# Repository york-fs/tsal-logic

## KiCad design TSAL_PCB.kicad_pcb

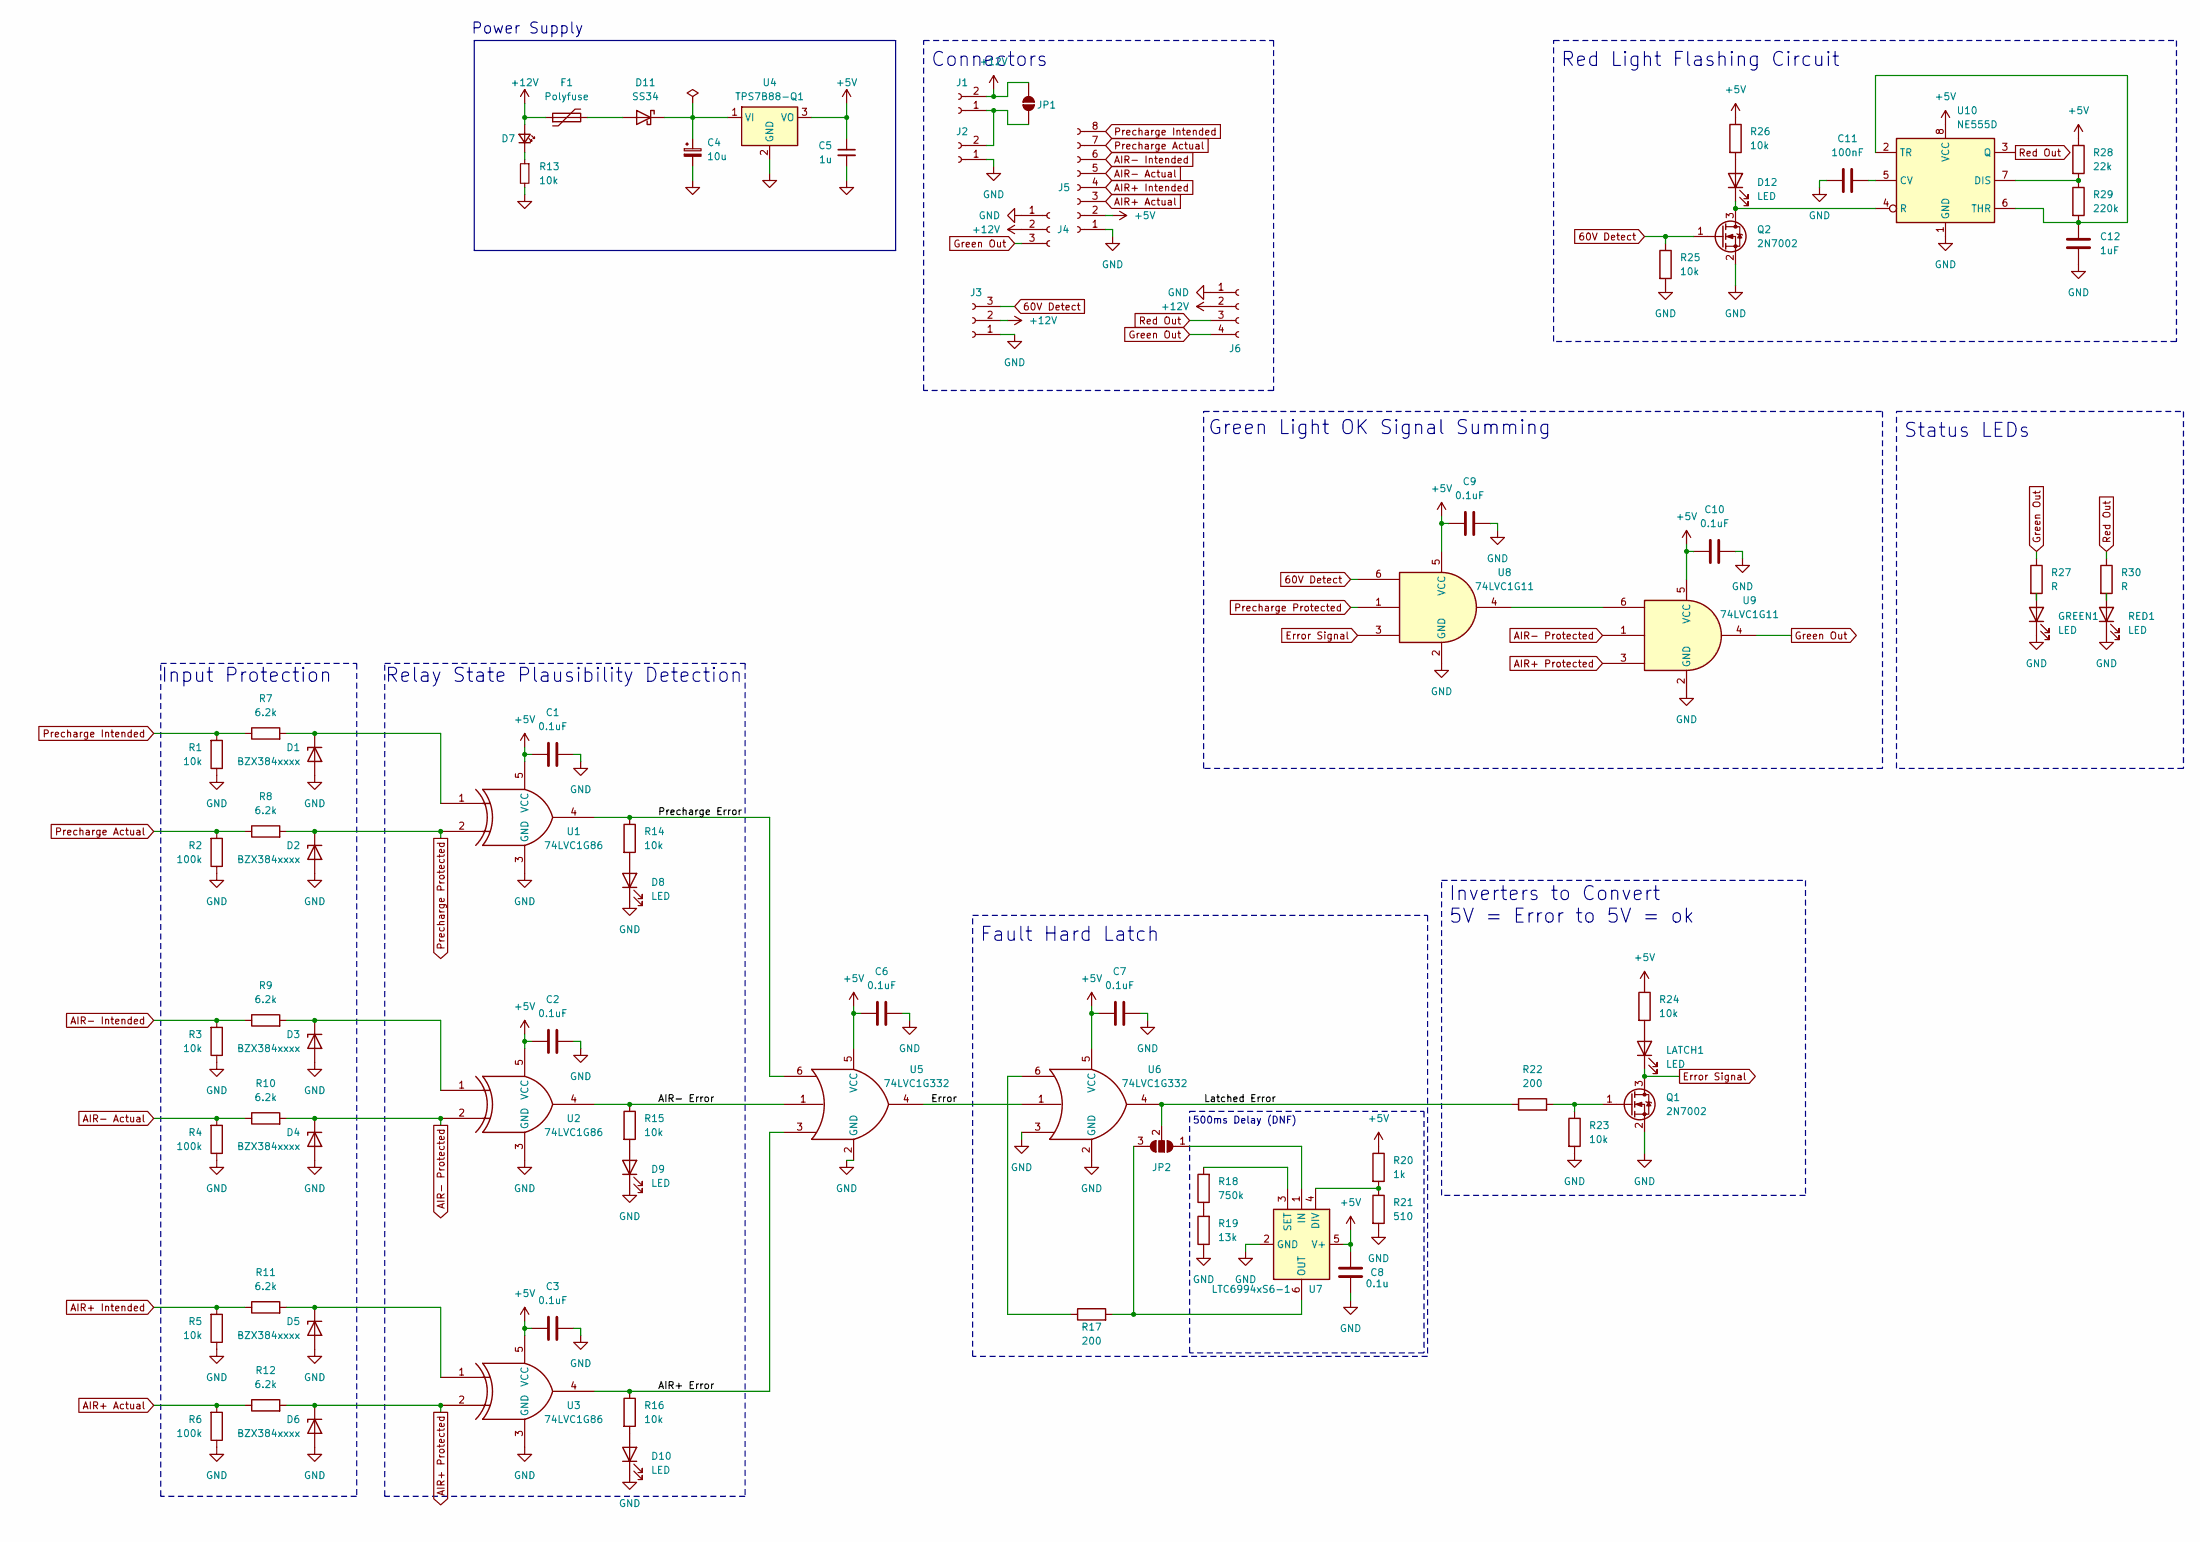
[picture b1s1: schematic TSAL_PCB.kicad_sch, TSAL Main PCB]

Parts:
C1, C2, C3, C6, C7, C9, C10: 0.1uF; C_0603_1608Metric
C4: 10u; CP_Elec_6.3x5.4
C5: 1u; C_0603_1608Metric
C8: 0.1u; C_0603_1608Metric
C11: 100nF; C_0603_1608Metric
C12: 1uF; C_0603_1608Metric
D1, D2, D3, D4, D5, D6: BZX384xxxx; D_SOD-323
D7: LED_Small; LED_0603_1608Metric
D8, D9, D10, D12: LED; LED_0603_1608Metric
D11: SS34; D_SMA
F1: Polyfuse; R_0805_2012Metric
GREEN1: LED; LED_0603_1608Metric
J1, J2: Conn_01x02_Socket; MolexMicrofitPlus1x2
J3, J4: Conn_01x03_Socket; MolexMicrofitPlus1x3
J5: Conn_01x08_Socket; MolexMicrofitPlus1x8
J6: Conn_01x04_Socket; MolexMicrofitPlus1x4
JP1: SolderJumper_2_Open; SolderJumper-2_P1.3mm_Open_RoundedPad1.0x1.5mm
JP2: SolderJumper_3_Open; SolderJumper-3_P1.3mm_Open_RoundedPad1.0x1.5mm_NumberLabels
LATCH1: LED; LED_0603_1608Metric
Q1, Q2: 2N7002; SOT-23
R1, R3, R5, R13, R14, R15, R16, R23, R24, R25, R26: 10k; R_0603_1608Metric
R2, R4, R6: 100k; R_0603_1608Metric
R7, R8, R9, R10, R11, R12: 6.2k; R_0603_1608Metric
R17, R22: 200; R_0603_1608Metric
R18: 750k; R_0603_1608Metric
R19: 13k; R_0603_1608Metric
R20: 1k; R_0603_1608Metric
R21: 510; R_0603_1608Metric
R27, R30: R; R_0603_1608Metric
R28: 22k; R_0603_1608Metric
R29: 220k; R_0603_1608Metric
RED1: LED; LED_0603_1608Metric
U1, U2, U3: 74LVC1G86; SOT-23-5
U4: TPS7B88-Q1; TO-252-2
U5, U6: 74LVC1G332; SOT-23-6
U7: LTC6994xS6-1; TSOT-23-6
U8, U9: 74LVC1G11; SOT-23-6
U10: NE555D; SOIC-8_3.9x4.9mm_P1.27mm

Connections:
60V Detect: J3.3, Q2.1 (G), R25.1, U8.6
+5V: C1.1, C2.1, C3.1, C5.1, C6.1, C7.1, C8.2, C9.1, C10.1, J5.2, R20.1, R24.1, R26.1, R28.1, U1.5 (VCC), U2.5 (VCC), U3.5 (VCC), U4.3 (VO), U5.5 (VCC), U6.5 (VCC), U7.5 (V+), U8.5 (VCC), U9.5 (VCC), U10.8 (VCC)
+12V: D7.2 (A), F1.1, J1.2, J3.2, J4.2, J6.2, JP1.2 (B)
/AIR+ Error: R16.1, U3.4, U5.3
/AIR- Error: R15.1, U2.4, U5.1
/Error: U5.4, U6.1
/Latched Error: JP2.2 (C), R22.1, U6.4
/Precharge Error: R14.1, U1.4, U5.6
AIR+ Actual: J5.3, R6.2, R12.1
AIR+ Intended: J5.4, R5.2, R11.1
AIR+ Protected: D6.1 (K), R12.2, U3.2, U9.3
AIR- Actual: J5.5, R4.2, R10.1
AIR- Intended: J5.6, R3.2, R9.1
AIR- Protected: D4.1 (K), R10.2, U2.2, U9.1
Error Signal: LATCH1.1 (K), Q1.3 (D), U8.3
GND: C1.2, C2.2, C3.2, C4.2, C5.2, C6.2, C7.2, C8.1, C9.2, C10.2, C11.2, C12.1, D1.2 (A), D2.2 (A), D3.2 (A), D4.2 (A), D5.2 (A), D6.2 (A), D8.1 (K), D9.1 (K), D10.1 (K), GREEN1.1 (K), J2.1, J3.1, J4.1, J5.1, J6.1, Q1.2 (S), Q2.2 (S), R1.1, R2.1, R3.1, R4.1, R5.1, R6.1, R13.2, R19.1, R21.2, R23.2, R25.2, RED1.1 (K), U1.3 (GND), U2.3 (GND), U3.3 (GND), U4.2 (GND), U5.2 (GND), U6.2 (GND), U6.3, U7.2 (GND), U8.2 (GND), U9.2 (GND), U10.1 (GND)
Green Out: J4.3, J6.4, R27.1, U9.4
unnamed: D1.1 (K), R7.2, U1.1
unnamed: D3.1 (K), R9.2, U2.1
unnamed: D5.1 (K), R11.2, U3.1
unnamed: D7.1 (K), R13.1
unnamed: D8.2 (A), R14.2
unnamed: D9.2 (A), R15.2
unnamed: D10.2 (A), R16.2
unnamed: D11.2 (A), F1.2
unnamed: C4.1, D11.1 (K), U4.1 (VI)
unnamed: D12.2 (A), R26.2
unnamed: D12.1 (K), Q2.3 (D), U10.4 (R)
unnamed: GREEN1.2 (A), R27.2
unnamed: J1.1, J2.2, JP1.1 (A)
unnamed: JP2.1 (A), U7.1 (IN)
unnamed: JP2.3 (B), R17.2, U7.6 (OUT)
unnamed: LATCH1.2 (A), R24.2
unnamed: Q1.1 (G), R22.2, R23.1
unnamed: R17.1, U6.6
unnamed: R18.1, R19.2
unnamed: R30.2, RED1.2 (A)
unnamed: R20.2, R21.1, U7.4 (DIV)
unnamed: R18.2, U7.3 (SET)
unnamed: U8.4, U9.6
unnamed: C11.1, U10.5 (CV)
unnamed: R28.2, R29.1, U10.7 (DIS)
unnamed: C12.2, R29.2, U10.2 (TR), U10.6 (THR)
Precharge Actual: J5.7, R2.2, R8.1
Precharge Intended: J5.8, R1.2, R7.1
Precharge Protected: D2.1 (K), R8.2, U1.2, U8.1
Red Out: J6.3, R30.1, U10.3 (Q)

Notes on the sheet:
Green Light OK Signal Summing
Relay State Plausibility Detection
Connectors
500ms Delay (DNF)
Power Supply
Inverters to Convert 5V = Error to 5V = ok
Input Protection
Fault Hard Latch
Red Light Flashing Circuit
Status LEDs

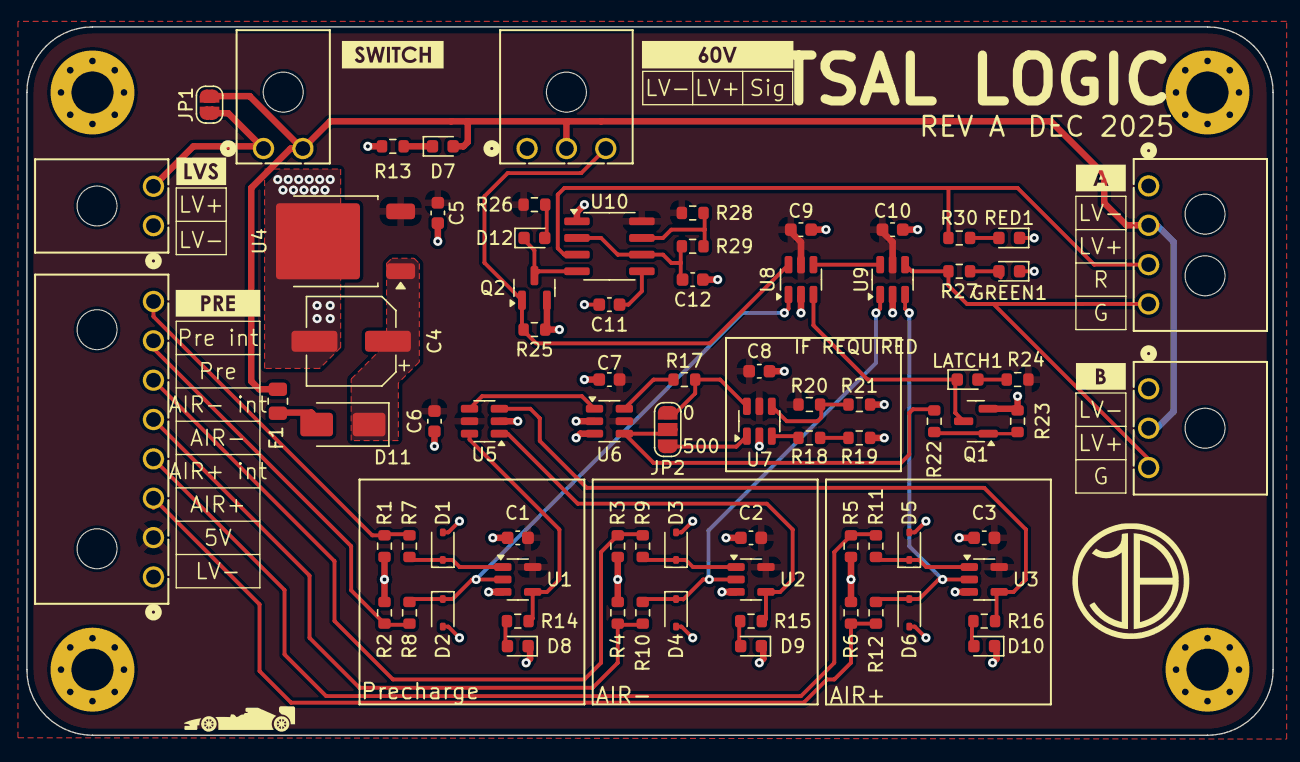
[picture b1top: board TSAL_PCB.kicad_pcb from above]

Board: 2 copper layers, 95.0 x 54.0 mm, 84 parts (0 on the bottom side), 47 nets.

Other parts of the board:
kibuzzard-69304CEA: G***; kibuzzard-69304CEA
kibuzzard-69304CF6: G***; kibuzzard-69304CF6
kibuzzard-69304CFD: G***; kibuzzard-69304CFD
kibuzzard-69304D07: G***; kibuzzard-69304D07
kibuzzard-69304E4B: G***; kibuzzard-69304E4B
kibuzzard-693052B2: G***; kibuzzard-693052B2
